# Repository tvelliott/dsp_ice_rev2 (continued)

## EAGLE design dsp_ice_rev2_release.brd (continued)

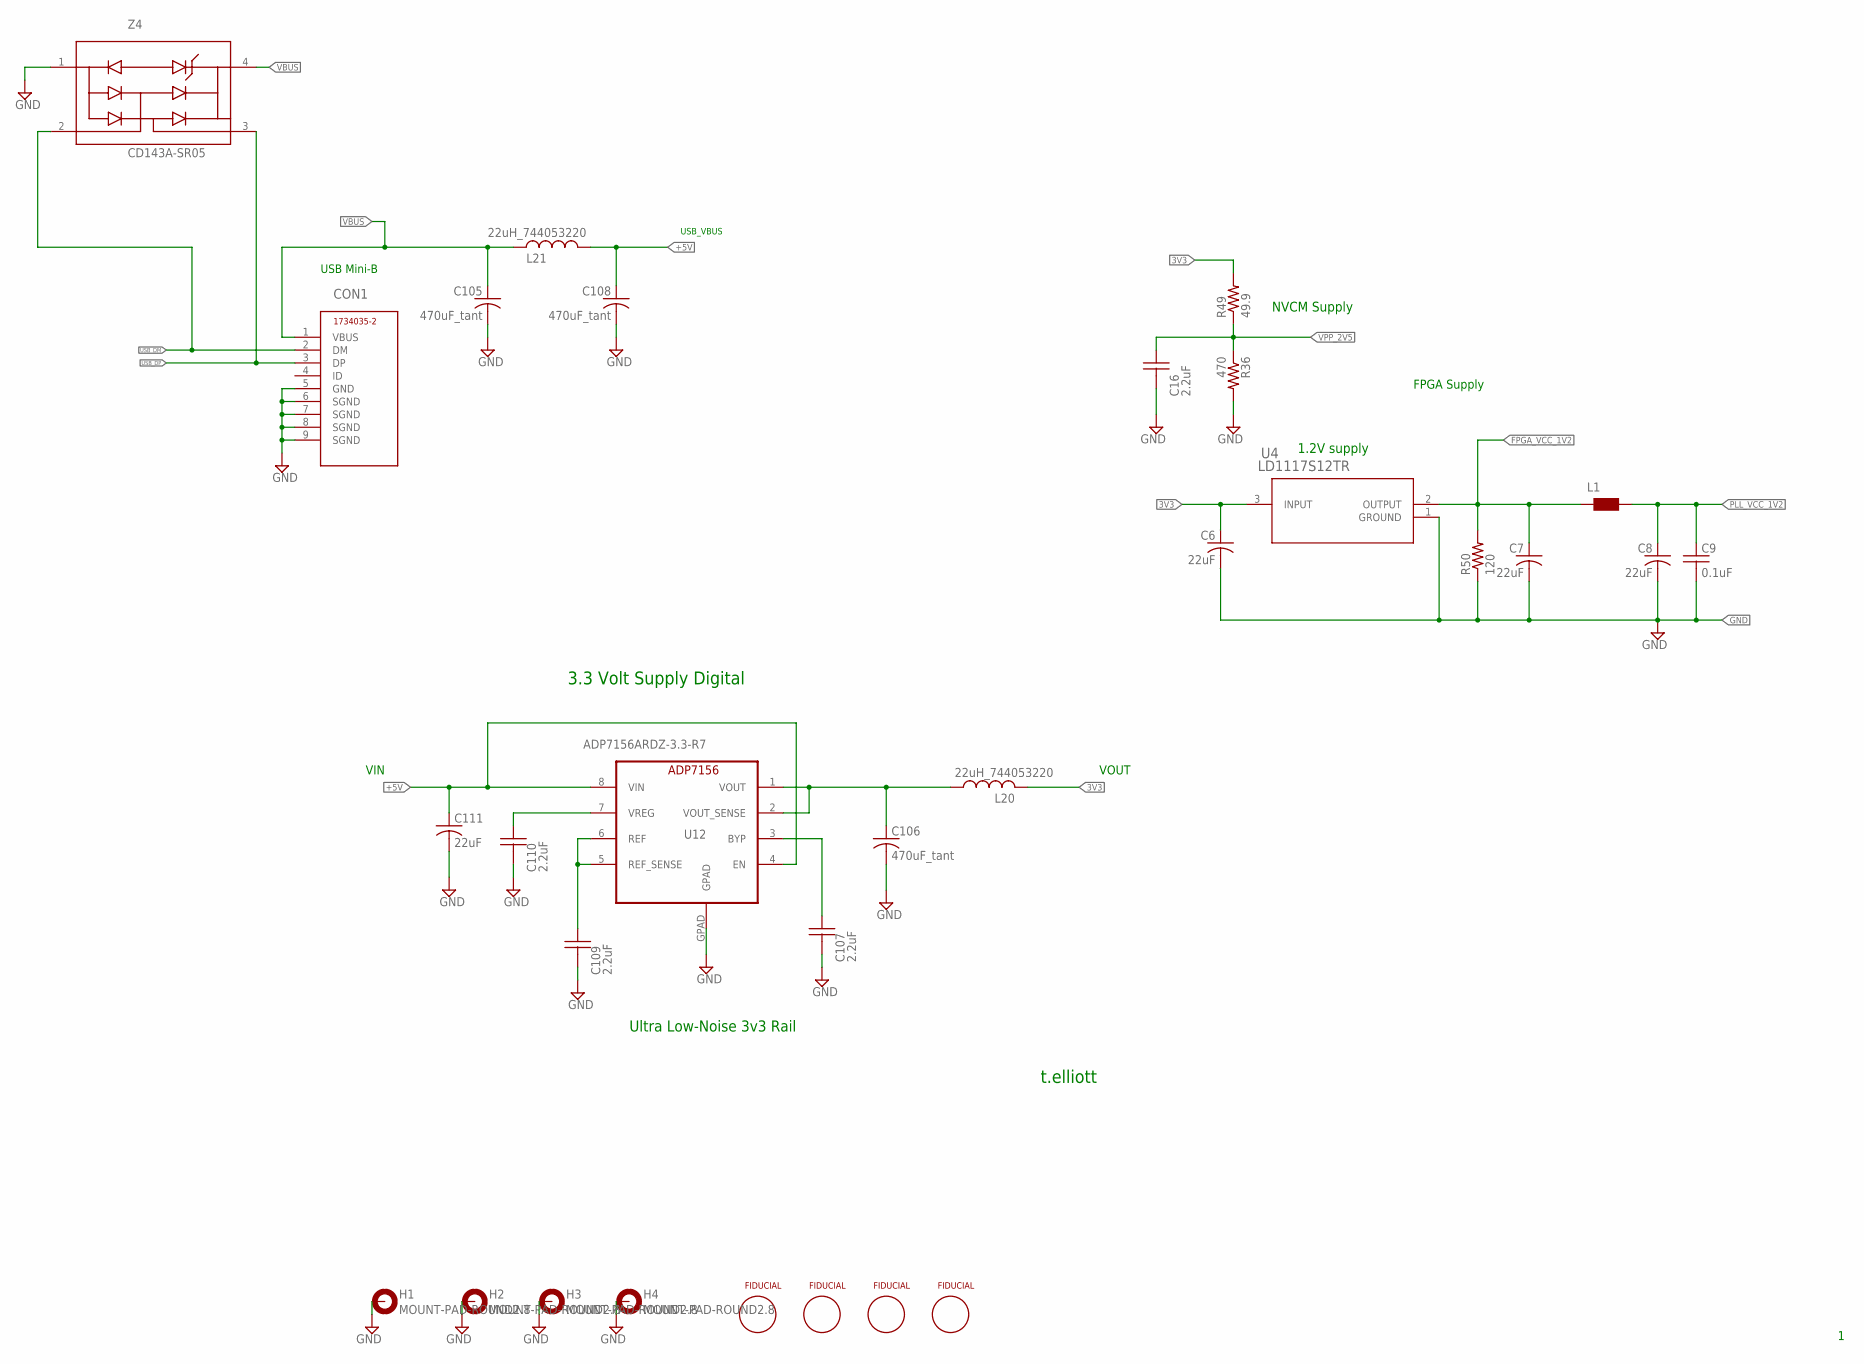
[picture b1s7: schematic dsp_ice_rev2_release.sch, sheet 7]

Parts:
C6, C7, C8, C111: 22uF; 1210K
C9: 0.1uF; C0603
C16, C107, C109, C110: 2.2uF; C0805
C105, C106, C108: 470uF_tant; 1210K
CON1: 1734035-2
FID1, FID2, FID3, FID4: FIDUCIALSMD; FIDUCIAL
H1, H2, H3, H4: MOUNT-PAD-ROUND2.8; 2,8-PAD
L1: WE-CBF_0603; 0603
L20, L21: 22uH_744053220; POWER-CHOKE_WE-TPC
R36: 470; R0402
R49: 49.9; R0603
R50: 120; R0603
U4: LD1117S12TR; SOT-223
U12: ADP7156ARDZ-3.3-R7; SO8
Z4: CD143A-SR05; SR2.8.TCT_1PRIMARY

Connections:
3V3: C6.A, L20.2, R49.2, U4.3 (INPUT); also elsewhere on the board
+5V: C108.A, C111.A, L21.1, U12.4 (EN), U12.8 (VIN); also elsewhere on the board
FPGA_VCC_1V2: C7.A, L1.1, R50.2, U4.2 (OUTPUT); also elsewhere on the board
GND: C6.C, C7.C, C8.C, C9.2, C16.2, C105.C, C106.C, C107.2, C108.C, C109.2, C110.2, C111.C, CON1.5 (GND), CON1.6 (SGND), CON1.7 (SGND), CON1.8 (SGND), CON1.9 (SGND), H1.B2,8, H2.B2,8, H3.B2,8, H4.B2,8, R36.2, R50.1, U4.1 (GROUND), U12.GPAD, Z4.1 (GND); also elsewhere on the board
unnamed: C106.A, L20.1, U12.1 (VOUT), U12.2 (VOUT_SENSE)
unnamed: C109.1, U12.5 (REF_SENSE), U12.6 (REF)
unnamed: C110.1, U12.7 (VREG)
unnamed: C107.1, U12.3 (BYP)
PLL_VCC_1V2: C8.A, C9.1, L1.2; also elsewhere on the board
USB_DM: CON1.2 (DM), Z4.2 (I/O); also elsewhere on the board
USB_DP: CON1.3 (DP), Z4.3 (I/O); also elsewhere on the board
VBUS: C105.A, CON1.1 (VBUS), L21.2, Z4.4 (REF)
VPP_2V5: C16.1, R36.1, R49.1; also elsewhere on the board

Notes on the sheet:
t.elliott
VIN
VOUT
3.3 Volt Supply Digital
USB Mini-B
USB_VBUS
1.2V supply
NVCM Supply
Ultra Low-Noise 3v3 Rail
FPGA Supply

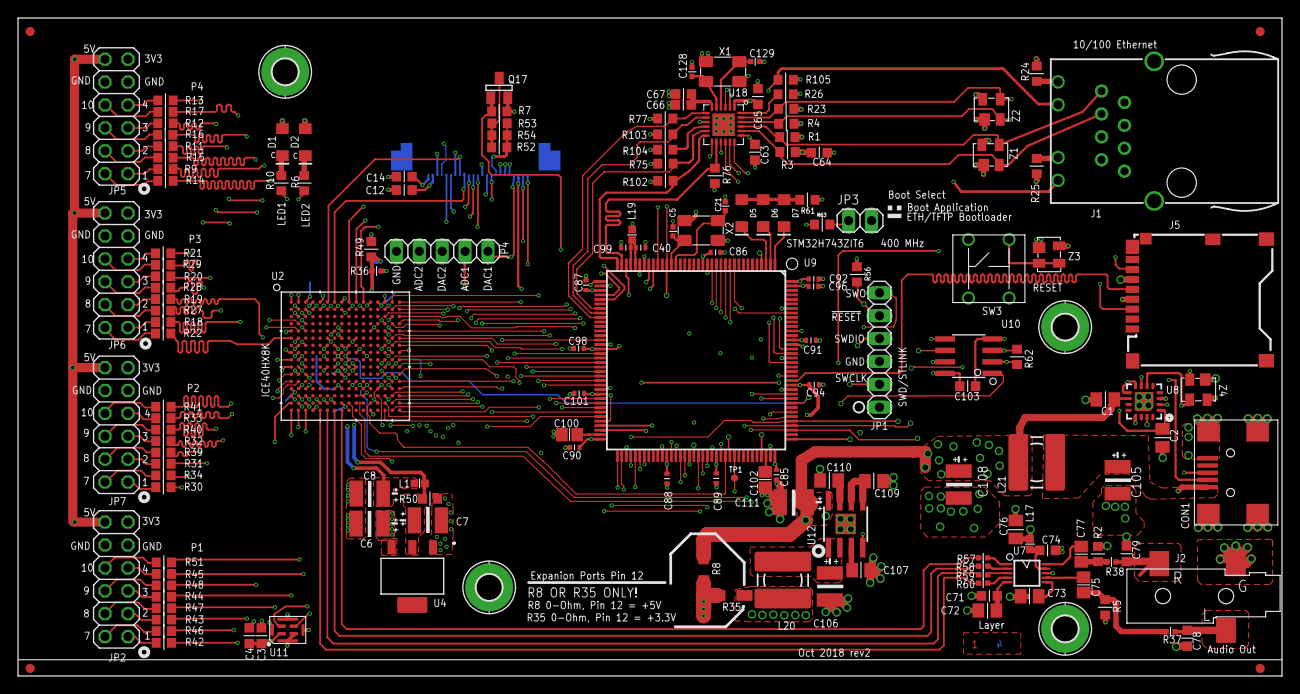
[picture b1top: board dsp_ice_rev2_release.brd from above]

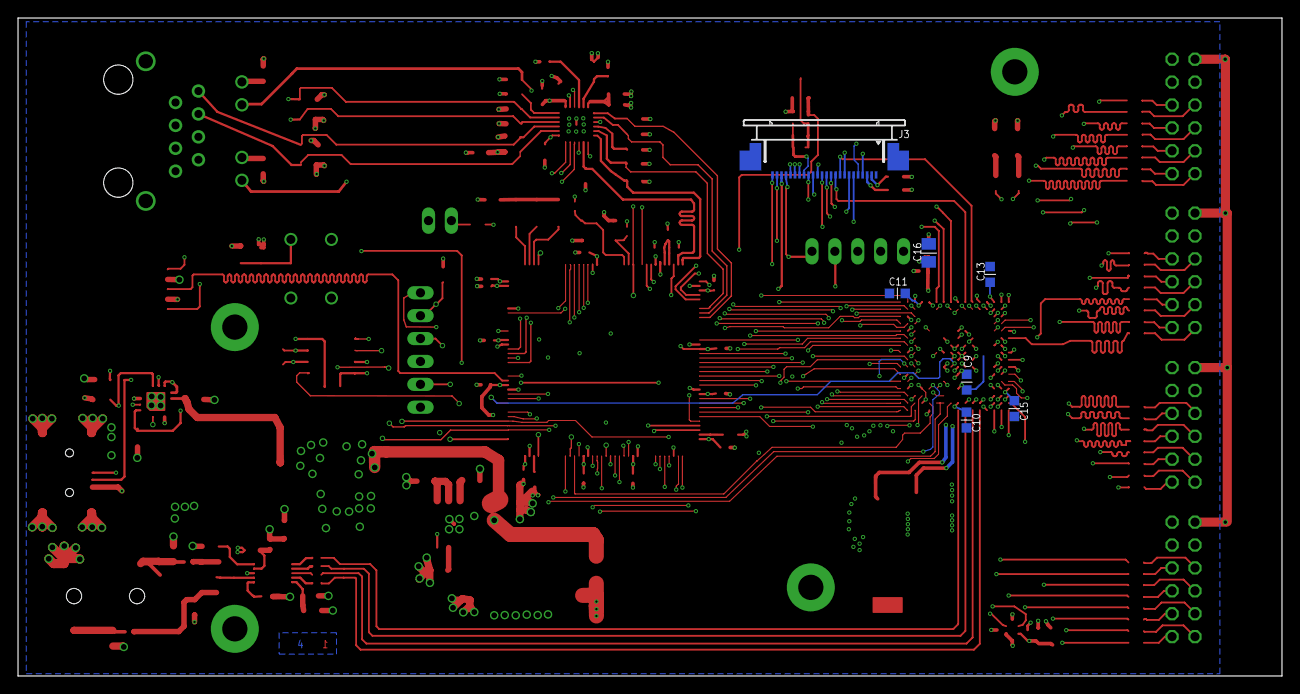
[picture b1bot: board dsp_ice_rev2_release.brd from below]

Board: 4 copper layers, 140.2 x 73.0 mm, 174 parts (7 on the bottom side), 214 nets.

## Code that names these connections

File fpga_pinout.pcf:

set_io F_MCLK H16 
set_io LED2 A1 
set_io LED3 A2 
set_io LED4 A5 
set_io clk_in R9 
set_io AUDIO_SDIN T8 
set_io AUDIO_SCLK T7 
set_io AUDIO_LRCLK T6 
set_io AUDIO_MCLK T5 
set_io CBSEL P13
set_io PMOD1_1 P2
set_io PMOD1_2 R2 
set_io PMOD1_3 T1 
set_io PMOD1_4 T3
set_io PMOD1_7 P1
set_io PMOD1_8 R1
set_io PMOD1_9 R3
set_io PMOD1_10 T2
set_io PMOD2_1 K1 
set_io PMOD2_2 L3
set_io PMOD2_3 M2 
set_io PMOD2_4 N3 
set_io PMOD2_7 K3 
set_io PMOD2_8 L1 
set_io PMOD2_9 M1 
set_io PMOD2_10 N2 
set_io PMOD3_1 F2 
set_io PMOD3_2 G3
set_io PMOD3_3 H1 
set_io PMOD3_4 J2 
set_io PMOD3_7 F1 
set_io PMOD3_8 G2 
set_io PMOD3_9 H2 
set_io PMOD3_10 J1 
set_io PMOD4_1 B3 
set_io PMOD4_2 C3 
set_io PMOD4_3 D3 
set_io PMOD4_4 E3 
set_io PMOD4_7 B2 
set_io PMOD4_8 C2 
set_io PMOD4_9 D2 
set_io PMOD4_10 E2 
set_io P_A6 A6 
set_io P_A7 A7 
set_io P_A9 A9 
set_io P_A10 A10 
set_io P_A11 A11 
set_io P_B6 B6 
set_io P_B7 B7 
set_io P_B8 B8 
set_io P_B9 B9 
set_io P_B11 B11 
set_io A0 C16 
set_io A1 T15 
set_io A2 R16 
set_io A3 R15 
set_io A4 P16 
set_io A5 P15 
set_io A6 N16 
set_io A7 M16 
set_io A8 M15 
set_io A9 L16 
set_io A10 T14 
set_io A11 R14  
set_io A12 P14 
set_io A13 L14 
set_io A14 D14 
set_io A15 C14 
set_io D0 D16 
set_io D1 D15 
set_io D2 B16 
set_io D3 B15 
set_io D4 A16 
set_io D5 A15 
set_io D6 E16 
set_io D7 F15 
set_io D8 F16 
set_io D9 G15 
set_io D10 G16 
set_io D11 J15 
set_io D12 J16 
set_io D13 K15 
set_io D14 K16 
set_io D15 T16 
set_io FSMC_NOE F14 
set_io FSMC_NWE H14 
set_io FSMC_NE1 J14 
set_io FSMC_NE4 K14 
set_io FSMC_NL_NADV B14
set_io FPGA_SPI_SCLK R10
set_io FPGA_SPI_MOSI P10
set_io FPGA_SPI_MISO N12
set_io FPGA_SPI_CS T13
set_io FSMC_CLK K9 

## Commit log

2020-05-16 added project icestorm stye fpga pinout definition
